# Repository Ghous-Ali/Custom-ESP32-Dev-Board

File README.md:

# Custom ESP32 Development Board

A from-scratch ESP32-WROOM-32E development board designed in KiCad 9.0.7 on a 4-layer PCB stackup.

## Features

- **MCU:** ESP32-WROOM-32E (WiFi + Bluetooth, dual-core Xtensa LX6)
- **USB-to-Serial:** CP2102N-A02-GQFN28 with full auto-programming support (DTR/RTS via 2N7002 MOSFETs)
- **Power:** AMS1117-3.3V LDO with 22µF + 100nF input/output filtering; external 5V input option with power path selection
- **ESD Protection:** ESD5Zxx TVS diodes on USB D+/D- lines
- **User Interface:** Boot button, Reset button, Power LED, User LED
- **I/O:** Dual 17-pin headers — breadboard-compatible, exposing all usable GPIOs
- **RF:** Antenna keep-out zone with 5mm clearance on all sides — no copper pour under antenna area
- **PCB:** 4-layer stackup (Signal – GND – Power – Signal), designed for clean return paths and RF performance

## Schematic Overview

| Block | Key Components | Notes |
|---|---|---|
| ESP32 Module | ESP32-WROOM-32E | 38 pins exposed via castellated pads |
| USB-to-Serial | CP2102N, 2N7002 × 2 | Auto-reset circuit for one-click flashing |
| Power Regulation | AMS1117-3.3, SS8050 | 5V USB or external → 3.3V rail |
| ESD Protection | ESD5Zxx × 2 | On USB data lines |
| Decoupling | 100nF × 8, 22µF × 2, 10µF, 4.7µF | Distributed across power pins |

## 4-Layer Stackup Rationale

| Layer | Function |
|---|---|
| F.Cu | Signal routing + component pads |
| In1.Cu | Continuous ground plane |
| In2.Cu | Power distribution (3.3V, 5V) |
| B.Cu | Signal routing + component pads |

A dedicated ground plane on layer 2 ensures low-impedance return paths for high-speed USB signals and minimises EMI. Separating power onto its own inner layer reduces noise coupling to signal traces.

## Design Decisions

- **Auto-reset circuit:** Uses two 2N7002 N-channel MOSFETs driven by DTR and RTS from the CP2102N. This allows tools like `esptool.py` to automatically put the ESP32 into bootloader mode — no manual button pressing needed during upload.
- **Antenna keep-out:** 5mm clearance enforced on all sides of the ESP32 antenna area. No copper, traces, or components in this zone to preserve WiFi/Bluetooth performance.
- **External 5V input:** A 3-pin header (J1) allows powering the board from an external 5V source (e.g., battery pack or bench supply) independently of USB, with SS8050-based switching.
- **Pull-up/pull-down network:** Strapping pins (IO0, IO2, IO5, IO15) are configured via resistor network for default boot-from-flash behaviour.

## Repository Structure

```
Custom_ESP_Dev_Board/
├── hardware/                      # KiCad project files (.kicad_pro, .kicad_sch, .kicad_pcb)
├── production/
│   ├── gerbers/                   # Fabrication files
│   ├── BOM.csv                    # Bill of Materials
│   └── pick-and-place.csv        # Assembly positions
├── docs/
│   ├── images/                    # 3D renders, PCB layout, schematic screenshots
│   └── schematic.pdf             # Exported schematic PDF
├── LICENSE
└── README.md
```

## Tools Used

- **EDA:** KiCad 9.0.7
- **PCB Layers:** 4
- **Design Rules:** JLCPCB 4-layer capabilities (adjust as needed for your fab)

## Getting Started

1. Clone this repo
2. Open the `.kicad_pro` file in KiCad 9.0.7+
3. Generate Gerbers from PCB editor → File → Fabrication Outputs
4. Upload to your preferred PCB fab (JLCPCB, PCBWay, etc.)

## References

- [ESP32-WROOM-32E Datasheet](https://www.espressif.com/sites/default/files/documentation/esp32-wroom-32e_esp32-wroom-32ue_datasheet_en.pdf)
- [ESP32-DevKitC V4 Reference Schematic](https://dl.espressif.com/dl/schematics/esp32_devkitc_v4-sch.pdf)
- [CP2102N Datasheet](https://www.silabs.com/documents/public/data-sheets/cp2102n-datasheet.pdf)

## Licence

This project is open-source hardware. See [LICENSE](LICENSE) for details.

---

Designed by **Ghous Ali** — Electronics & Embedded Systems Engineer  
[LinkedIn](https://www.linkedin.com/in/ghousali13/) · [Email](Ghousali1019@email.com)

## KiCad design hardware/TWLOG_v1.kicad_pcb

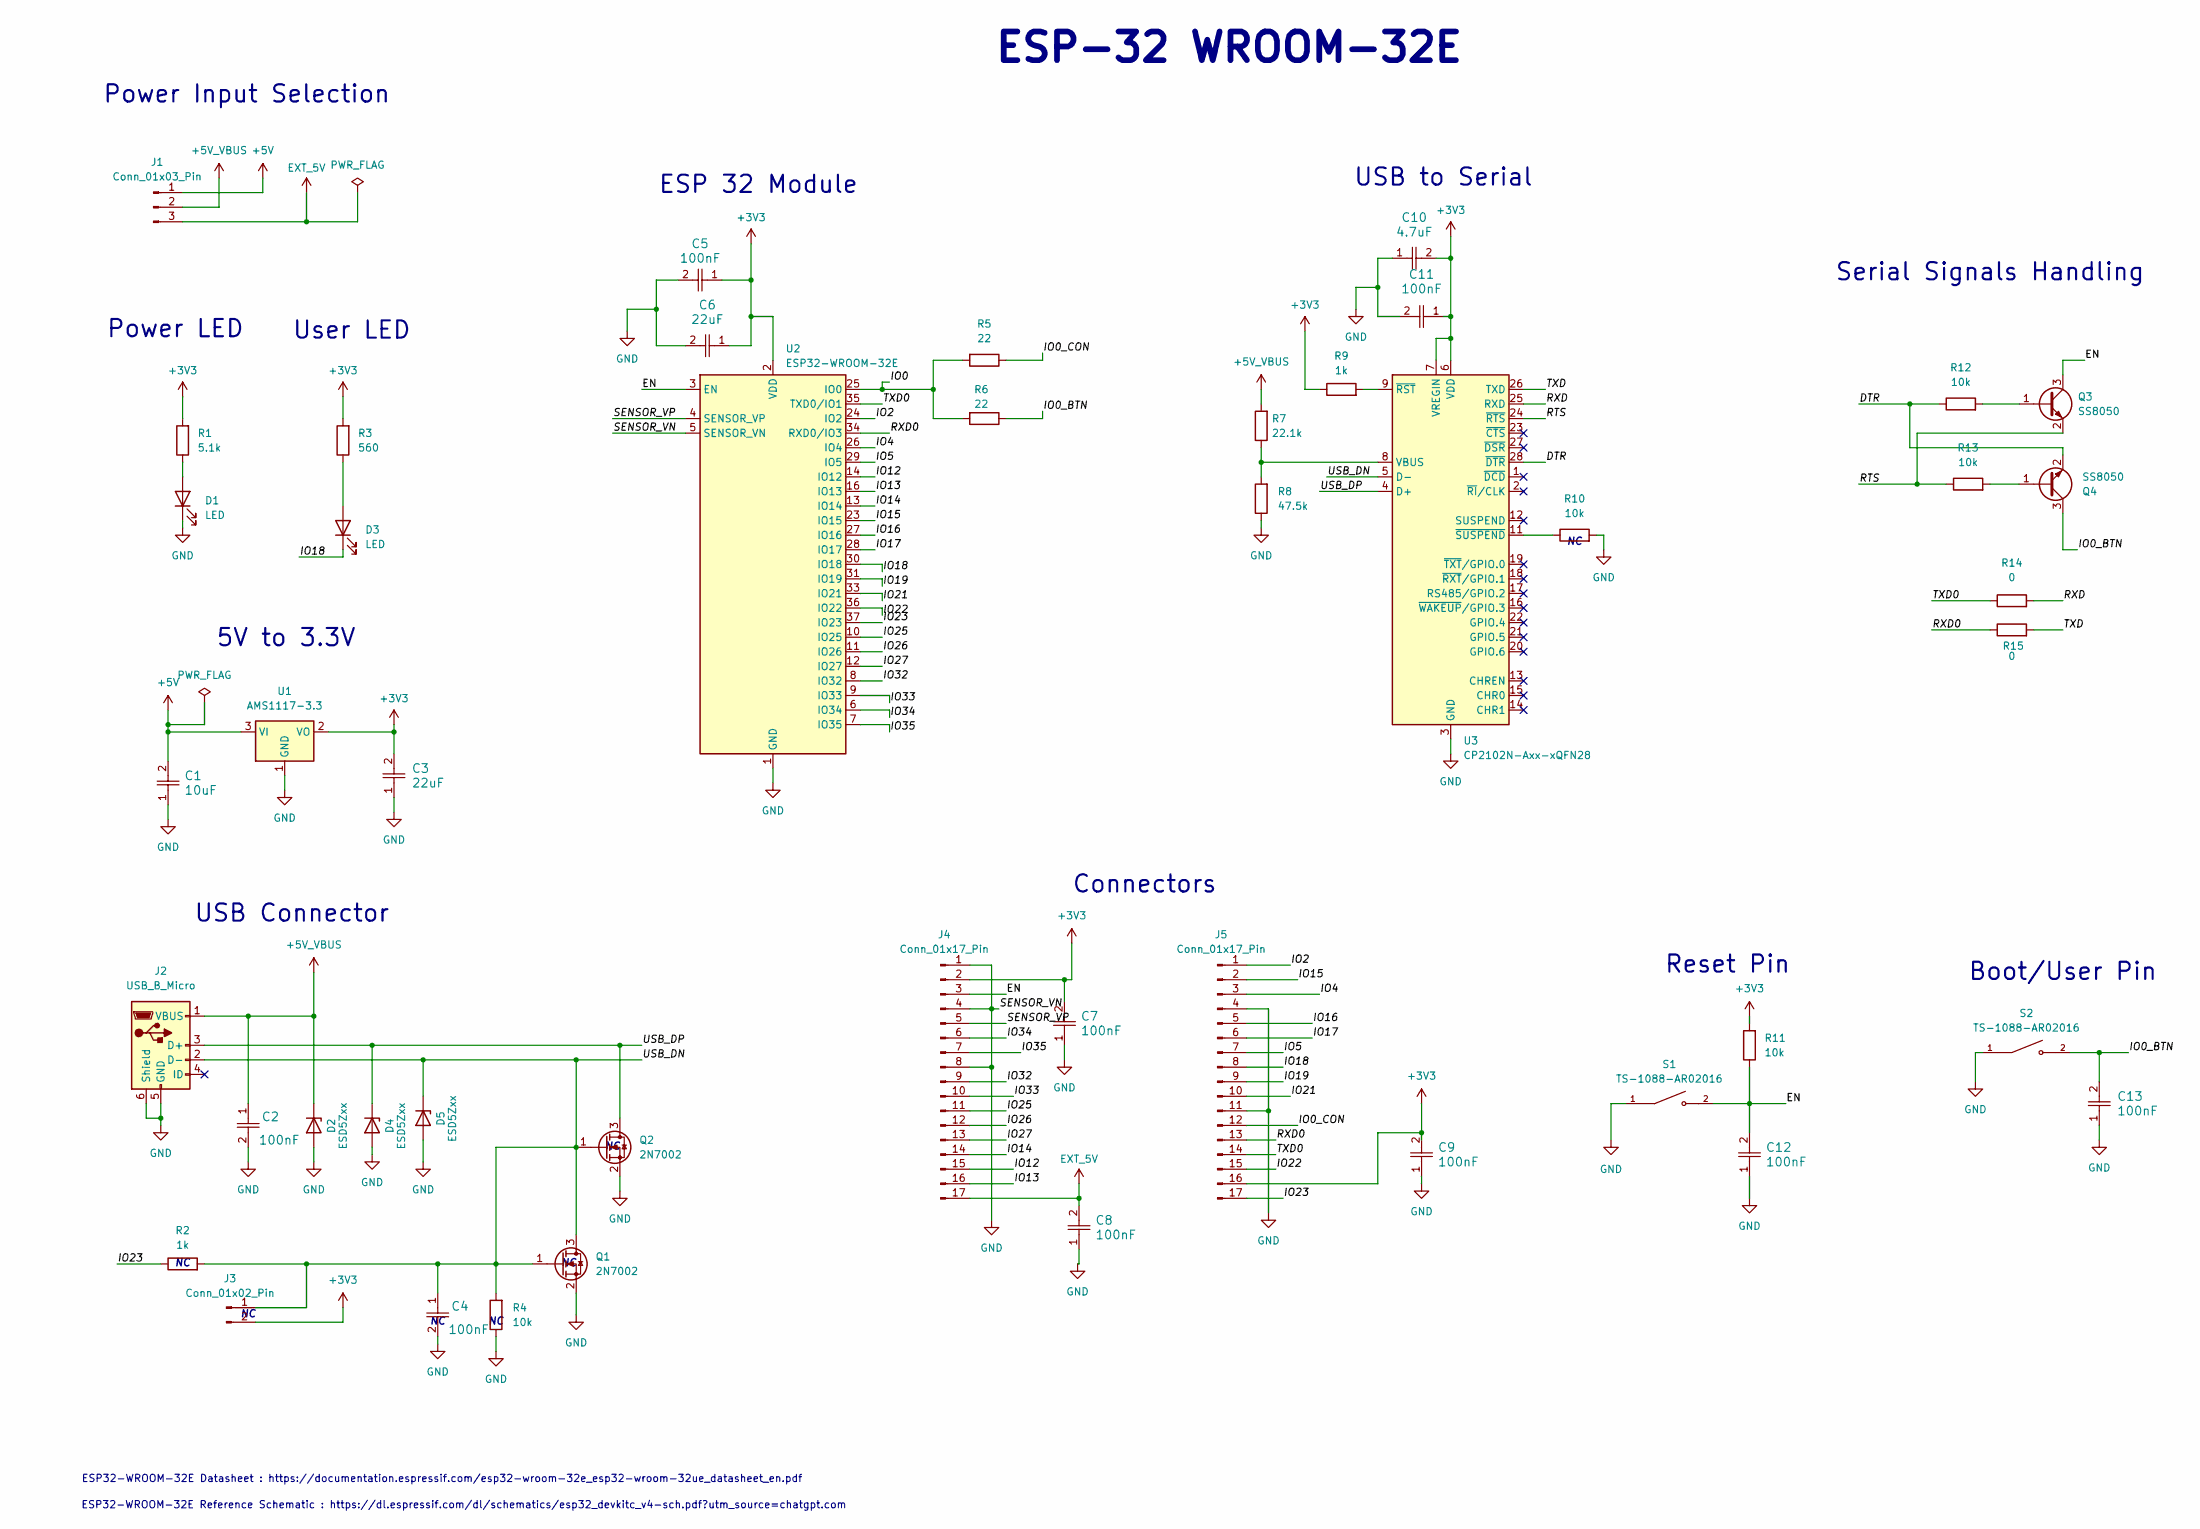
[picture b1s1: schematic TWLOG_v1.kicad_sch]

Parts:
C1: 10uF; C_0603_1608Metric
C2, C4, C5, C7, C8, C9, C11, C12, C13: 100nF; C_0402_1005Metric
C3, C6: 22uF; C_0603_1608Metric
C10: 4.7uF; C_0402_1005Metric
D1, D3: LED; LED_0805_2012Metric
D2, D4, D5: ESD5Zxx; D_SOD-523
J1: Conn_01x03_Pin; PinHeader_1x03_P1.27mm_Vertical
J2: USB_B_Micro; USB_Micro-B_Molex-105017-0001
J3: Conn_01x02_Pin; PinHeader_1x02_P1.27mm_Horizontal
J4, J5: Conn_01x17_Pin; Molex_SL_171971-0017_1x17_P2.54mm_Vertical
Q1, Q2: 2N7002; SOT-323_SC-70
Q3, Q4: SS8050; SOT-323_SC-70
R1: 5.1k; R_0402_1005Metric
R2, R9: 1k; R_0402_1005Metric
R3: 560; R_0402_1005Metric
R4, R10, R11, R12, R13: 10k; R_0402_1005Metric
R5, R6: 22; R_0402_1005Metric
R7: 22.1k; R_0402_1005Metric
R8: 47.5k; R_0402_1005Metric
R14, R15: 0; R_0402_1005Metric
S1, S2: TS-1088-AR02016; SW_TS-1088-AR02016; PARTREV N/A
U1: AMS1117-3.3; SOT-223-3_TabPin2
U2: ESP32-WROOM-32E; ESP32-WROOM-32D
U3: CP2102N-Axx-xQFN28; QFN-28-1EP_5x5mm_P0.5mm_EP3.35x3.35mm

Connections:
+3V3: C3.2, C5.1, C6.1, C7.2, C9.2, C10.2, C11.1, J3.2, J4.2, J5.16, R1.2, R3.2, R9.1, R11.2, U1.2 (VO), U2.2 (VDD), U3.6 (VDD), U3.7 (VREGIN)
+5V: C1.2, J1.1, U1.3 (VI)
+5V_VBUS: C2.1, D2.1 (K), J1.2, J2.1 (VBUS), R7.2
/DTR: Q4.2 (E), R12.1, U3.28 (~DTR)
/EN: C12.2, J4.3, Q3.3 (C), R11.1, S1.2, U2.3 (EN)
/IO0: R5.2, R6.2, U2.25 (IO0)
/IO0_BTN: C13.2, Q4.3 (C), R6.1, S2.2
/IO0_CON: J5.12, R5.1
/IO2: J5.1, U2.24 (IO2)
/IO4: J5.3, U2.26 (IO4)
/IO5: J5.7, U2.29 (IO5)
/IO12: J4.15, U2.14 (IO12)
/IO13: J4.16, U2.16 (IO13)
/IO14: J4.14, U2.13 (IO14)
/IO15: J5.2, U2.23 (IO15)
/IO16: J5.5, U2.27 (IO16)
/IO17: J5.6, U2.28 (IO17)
/IO18: D3.1 (K), J5.8, U2.30 (IO18)
/IO19: J5.9, U2.31 (IO19)
/IO21: J5.10, U2.33 (IO21)
/IO22: J5.15, U2.36 (IO22)
/IO23: J5.17, R2.1, U2.37 (IO23)
/IO25: J4.11, U2.10 (IO25)
/IO26: J4.12, U2.11 (IO26)
/IO27: J4.13, U2.12 (IO27)
/IO32: J4.9, U2.8 (IO32)
/IO33: J4.10, U2.9 (IO33)
/IO34: J4.6, U2.6 (IO34)
/IO35: J4.7, U2.7 (IO35)
/RTS: Q3.2 (E), R13.1, U3.24 (~RTS)
/RXD: R14.2, U3.25 (RXD)
/RXD0: J5.13, R15.1, U2.34 (RXD0/IO3)
/SENSOR_VP: J4.5, U2.4 (SENSOR_VP)
/TXD: R15.2, U3.26 (TXD)
/TXD0: J5.14, R14.1, U2.35 (TXD0/IO1)
/USB_DN: C4.1, D5.1 (K), J2.2 (D-), J3.1, Q1.1 (G), Q1.3 (D), Q2.1 (G), R2.2, R4.2, U3.5 (D-)
/USB_DP: D4.1 (K), J2.3 (D+), Q2.3 (D), U3.4 (D+)
EXT_5V: C8.2, J1.3, J4.17
GND: C1.1, C2.2, C3.1, C4.2, C5.2, C6.2, C7.1, C8.1, C9.1, C10.1, C11.2, C12.1, C13.1, D1.1 (K), D2.2 (A), D4.2 (A), D5.2 (A), J2.5 (GND), J2.6 (Shield), J4.1, J4.4, J4.8, J5.4, J5.11, Q1.2 (S), Q2.2 (S), R4.1, R8.1, R10.2, S1.1, S2.1, U1.1 (GND), U2.1 (GND), U2.5 (SENSOR_VN), U2.15 (GND), U2.38 (GND), U2.39 (GND), U3.3 (GND), U3.29 (GND)
unnamed: D1.2 (A), R1.1
unnamed: D3.2 (A), R3.1
unnamed: Q3.1 (B), R12.2
unnamed: Q4.1 (B), R13.2
unnamed: R7.1, R8.2, U3.8 (VBUS)
unnamed: R9.2, U3.9 (~RST)
unnamed: R10.1, U3.11 (~SUSPEND)

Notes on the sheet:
Serial Signals Handling
Connectors
ESP32-WROOM-32E Datasheet : https://documentation.espressif.com/esp32-wroom-32e_esp32-wroom-32ue_datasheet_en.pdf
Power LED
Reset Pin
ESP32-WROOM-32E Reference Schematic : https://dl.espressif.com/dl/schematics/esp32_devkitc_v4-sch.pdf?utm_source=chatgpt.com
Power Input Selection
USB Connector
USB to Serial
ESP-32 WROOM-32E
User LED
Boot/User Pin
ESP 32 Module
5V to 3.3V

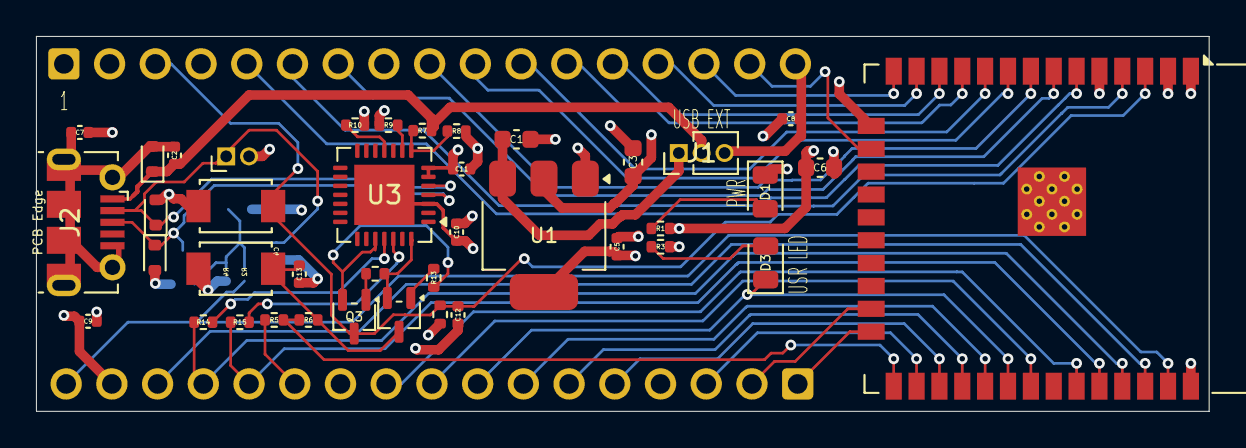
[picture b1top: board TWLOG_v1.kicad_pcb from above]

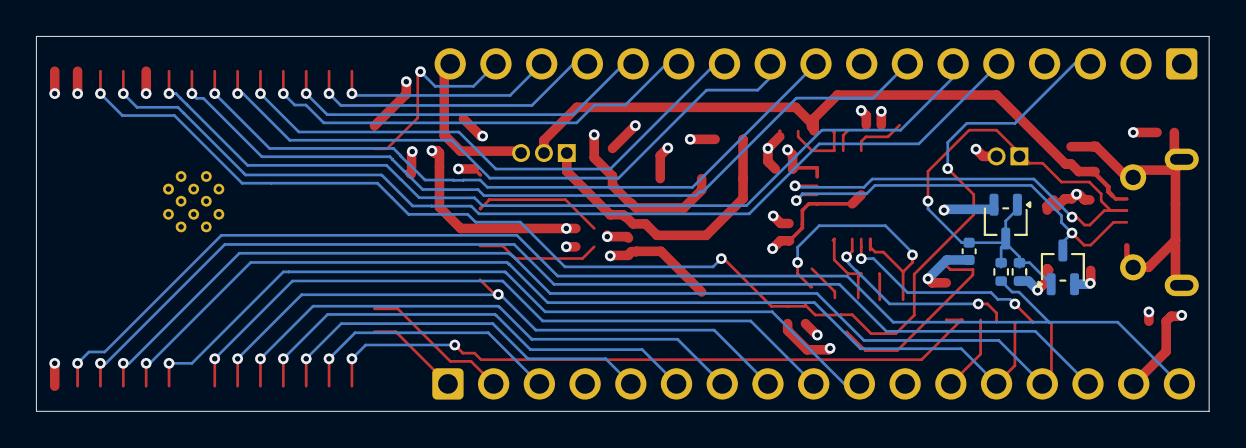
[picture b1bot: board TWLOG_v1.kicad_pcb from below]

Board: 4 copper layers, 65.2 x 20.8 mm, 47 parts (5 on the bottom side), 46 nets.

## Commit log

2026-05-11 Add KiCad project files
2026-05-11 Add fabrication outputs
2026-05-11 Add schematic PDF
